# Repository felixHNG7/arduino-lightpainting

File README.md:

# arduino-lightpainting
A projet for an arduino based objet to create light painting images

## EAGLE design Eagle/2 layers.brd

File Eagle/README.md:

# arduino-lightpainting
The folder were we'll place the PCB schematics

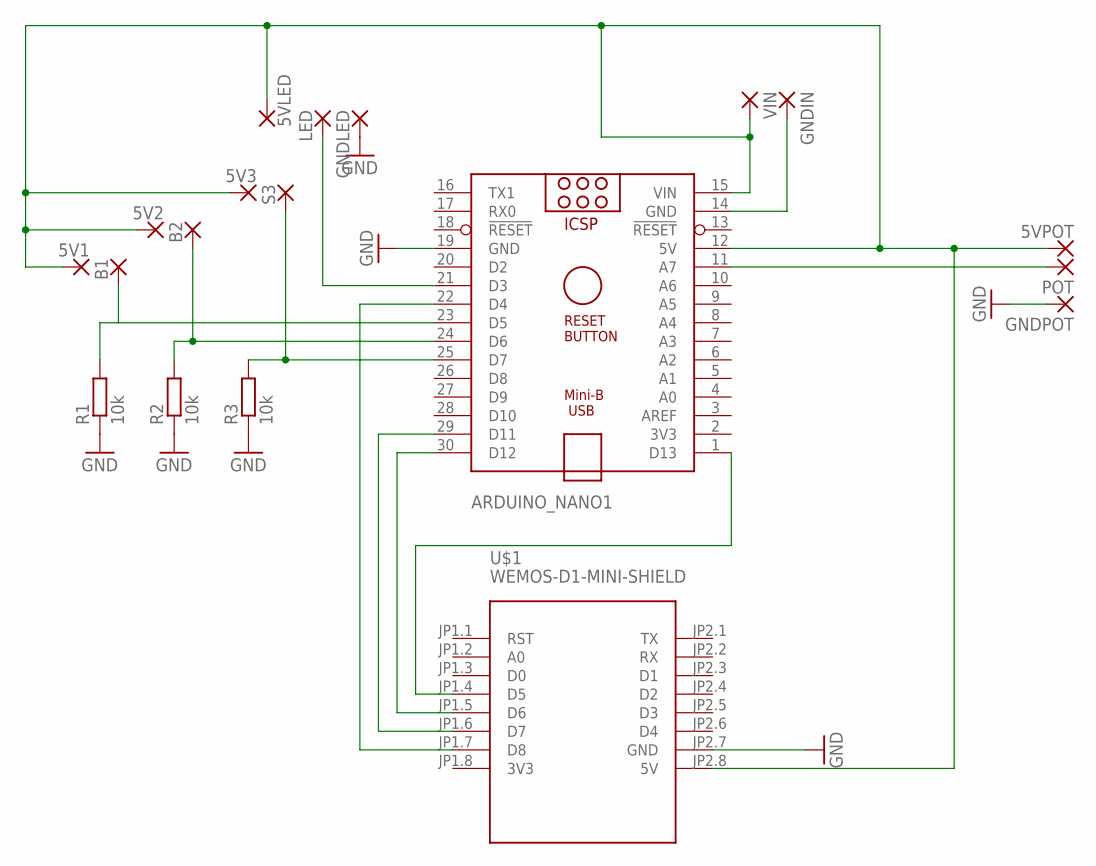
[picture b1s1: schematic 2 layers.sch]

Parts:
5V1, 5V2, 5V3, 5VLED, 5VPOT: 1,6/0,8
ARDUINO_NANO1: ARDUINO_NANO
B1, B2: 1,6/0,8
GNDIN: 1,6/0,8
GNDLED: 1,6/0,8
GNDPOT: 1,6/0,8
LED: 1,6/0,8
POT: 1,6/0,8
R1, R2, R3: 10k; 0207/7
S3: 1,6/0,8
U$1: WEMOS-D1-MINI-SHIELD
VIN: 1,6/0,8

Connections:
3V3: U$1.JP1.8 (3V3)
GND: ARDUINO_NANO1.19 (GND), GNDLED.1, GNDPOT.1, R1.1, R2.1, R3.1, U$1.JP2.7 (GND)
unnamed: 5V1.1, 5V2.1, 5V3.1, 5VLED.1, 5VPOT.1, ARDUINO_NANO1.12 (5V), ARDUINO_NANO1.15 (VIN), U$1.JP2.8 (5V), VIN.1
unnamed: ARDUINO_NANO1.14 (GND), GNDIN.1
unnamed: ARDUINO_NANO1.11 (A7), POT.1
unnamed: ARDUINO_NANO1.1 (D13), U$1.JP1.4 (D5)
unnamed: ARDUINO_NANO1.30 (D12), U$1.JP1.5 (D6)
unnamed: ARDUINO_NANO1.29 (D11), U$1.JP1.6 (D7)
unnamed: ARDUINO_NANO1.25 (D7), R3.2, S3.1
unnamed: ARDUINO_NANO1.22 (D4), U$1.JP1.7 (D8)
unnamed: ARDUINO_NANO1.24 (D6), B2.1, R2.2
unnamed: ARDUINO_NANO1.23 (D5), B1.1, R1.2
unnamed: ARDUINO_NANO1.21 (D3), LED.1

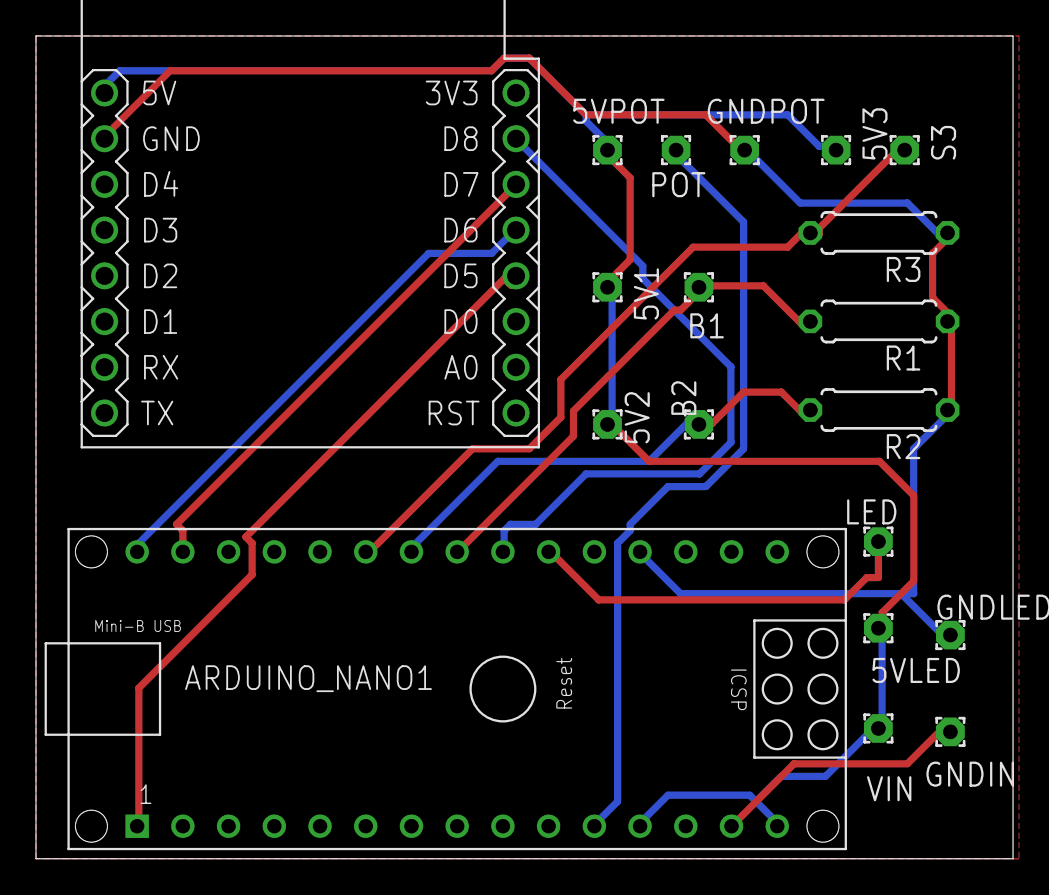
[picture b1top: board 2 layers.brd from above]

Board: 2 copper layers, 54.3 x 45.7 mm, 19 parts (0 on the bottom side), 12 nets.

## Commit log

2020-01-15 New soft version

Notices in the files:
parts and their libraries:
diy-modules: Released under the Creative Commons Attribution 4.0 International License: http://creativecommons.org/licenses/by/4.0
